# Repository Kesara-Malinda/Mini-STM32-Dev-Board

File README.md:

# Mini-STM32-Dev-Board

Designed using KiCad 6.0

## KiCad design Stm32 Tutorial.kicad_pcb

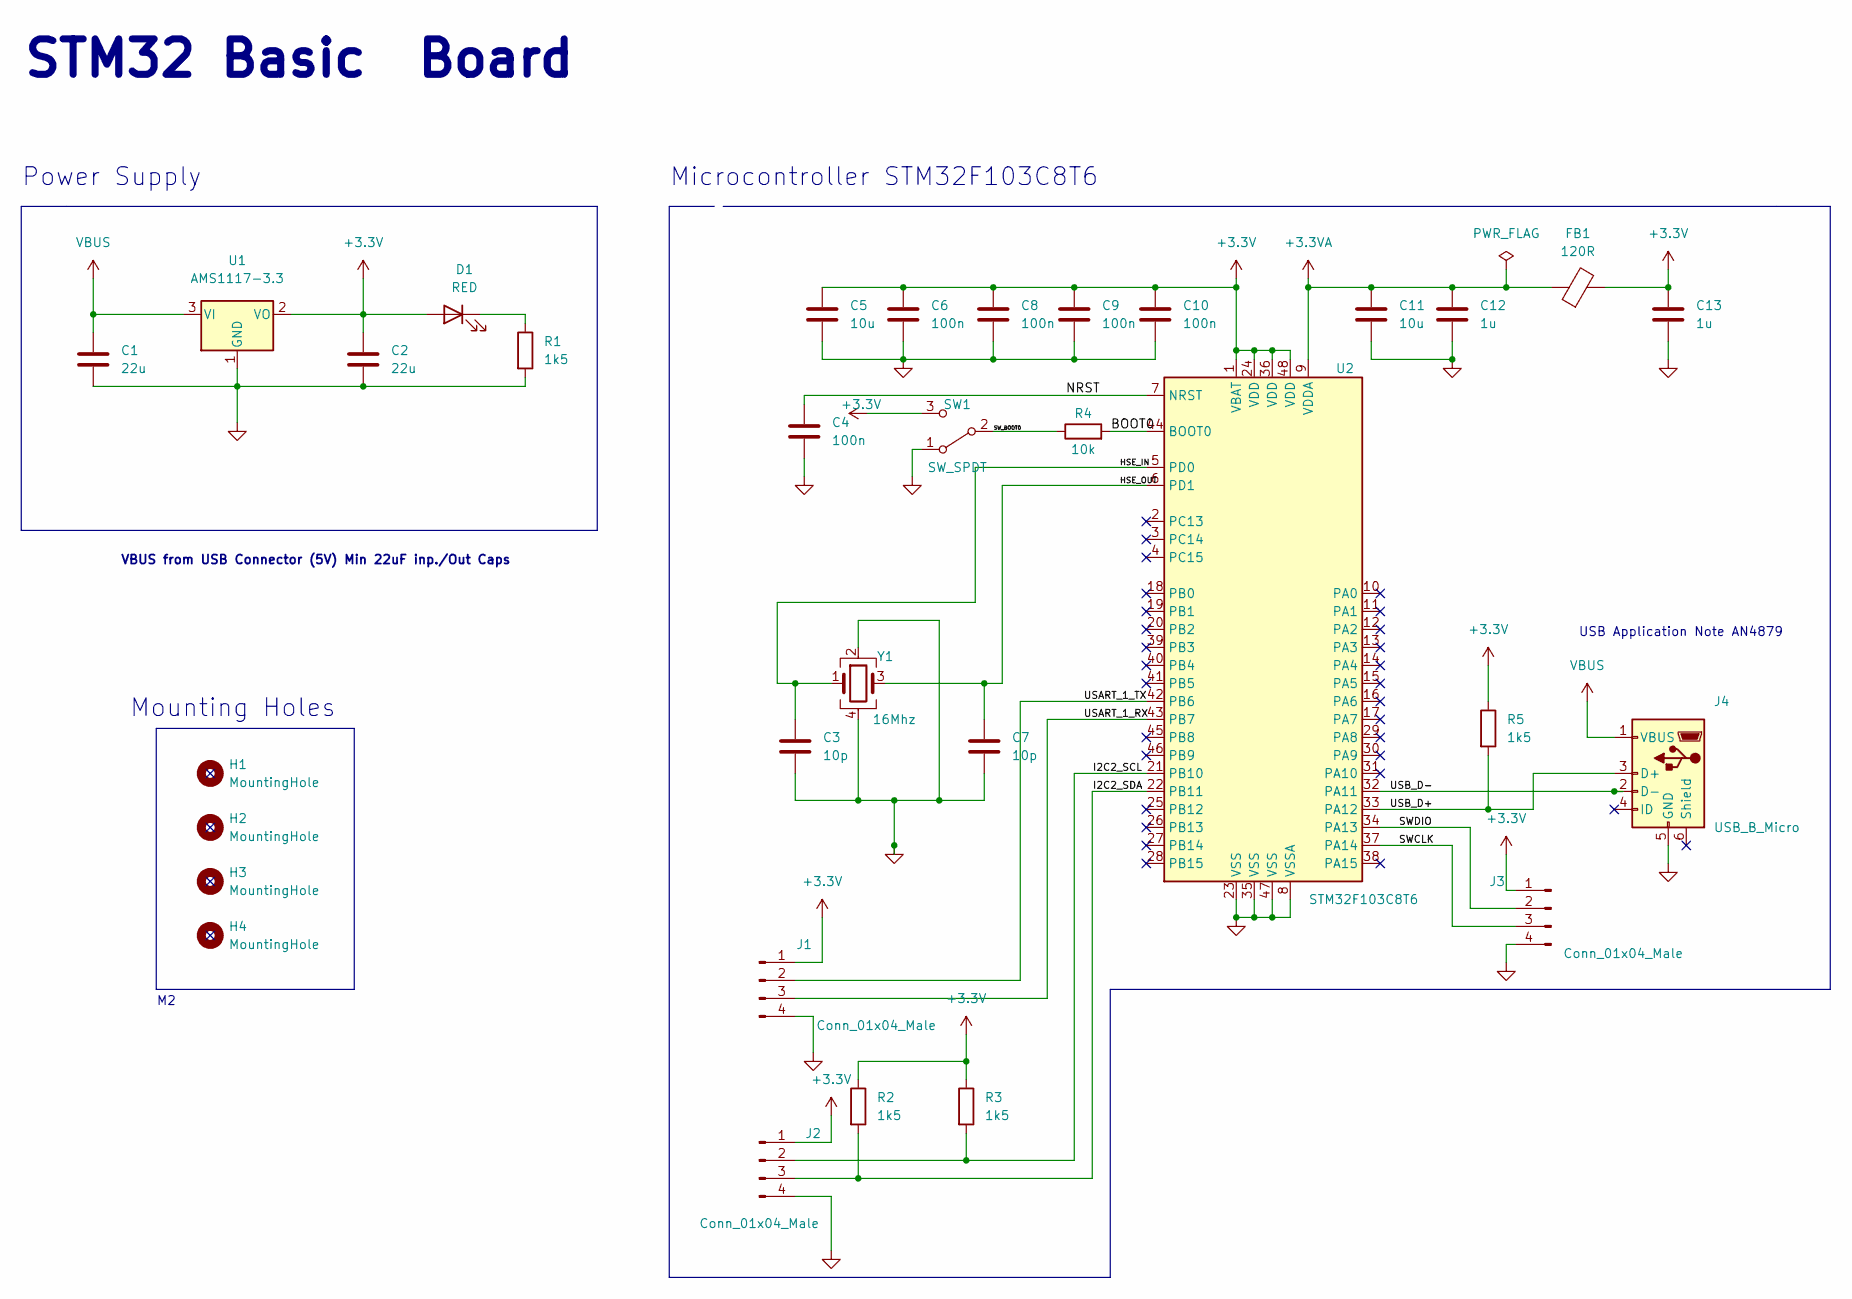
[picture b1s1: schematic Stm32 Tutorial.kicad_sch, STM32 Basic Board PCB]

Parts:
C1, C2: 22u; C_0805_2012Metric
C3, C7: 10p; C_0402_1005Metric
C4, C6, C8, C9, C10: 100n; C_0402_1005Metric
C5: 10u; C_0603_1608Metric
C11: 10u; C_0402_1005Metric
C12, C13: 1u; C_0402_1005Metric
D1: RED; LED_0603_1608Metric
FB1: 120R; L_0603_1608Metric
H1, H2, H3, H4: MountingHole; MountingHole_2.2mm_M2
J1, J2, J3: Conn_01x04_Male; PinHeader_1x04_P2.54mm_Vertical
J4: USB_B_Micro; USB_Micro-B_Wuerth_629105150521
R1, R2, R3, R5: 1k5; R_0402_1005Metric
R4: 10k; R_0402_1005Metric
SW1: SW_SPDT; SW_SPDT_PCM12
U1: AMS1117-3.3; SOT-223-3_TabPin2
U2: STM32F103C8T6; LQFP-48_7x7mm_P0.5mm
Y1: 16Mhz; Crystal_SMD_3225-4Pin_3.2x2.5mm_HandSoldering

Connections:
+3.3V: C2.1, C5.1, C6.1, C8.1, C9.1, C10.1, C13.1, D1.2 (A), FB1.2, J1.1, J2.1, J3.1, R2.1, R3.1, R5.1, SW1.3 (C), U1.2 (VO), U2.1 (VBAT), U2.24 (VDD), U2.36 (VDD), U2.48 (VDD)
+3.3VA: C11.1, C12.1, FB1.1, U2.9 (VDDA)
/BOOT0: R4.2, U2.44 (BOOT0)
/HSE_IN: C3.1, U2.5 (PD0), Y1.1
/HSE_OUT: C7.1, U2.6 (PD1), Y1.3
/I2C2_SCL: J2.2, R3.2, U2.21 (PB10)
/I2C2_SDA: J2.3, R2.2, U2.22 (PB11)
/NRST: C4.1, U2.7 (NRST)
/SWCLK: J3.3, U2.37 (PA14)
/SWDIO: J3.2, U2.34 (PA13)
/SW_BOOT0: R4.1, SW1.2 (B)
/USART_1_RX: J1.3, U2.43 (PB7)
/USART_1_TX: J1.2, U2.42 (PB6)
/USB_D+: J4.3 (D+), R5.2, U2.33 (PA12)
/USB_D-: J4.2 (D-), U2.32 (PA11)
GND: C1.2, C2.2, C3.2, C4.2, C5.2, C6.2, C7.2, C8.2, C9.2, C10.2, C11.2, C12.2, C13.2, J1.4, J2.4, J3.4, J4.5 (GND), J4.6 (Shield), R1.2, SW1.1 (A), U1.1 (GND), U2.8 (VSSA), U2.23 (VSS), U2.35 (VSS), U2.47 (VSS), Y1.2, Y1.4
unnamed: D1.1 (K), R1.1
VBUS: C1.1, J4.1 (VBUS), U1.3 (VI)

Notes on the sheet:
VBUS from USB Connector (5V) Min 22uF inp./Out Caps
Microcontroller STM32F103C8T6
Mounting Holes
USB Application Note AN4879
STM32 Basic Board
Power Supply

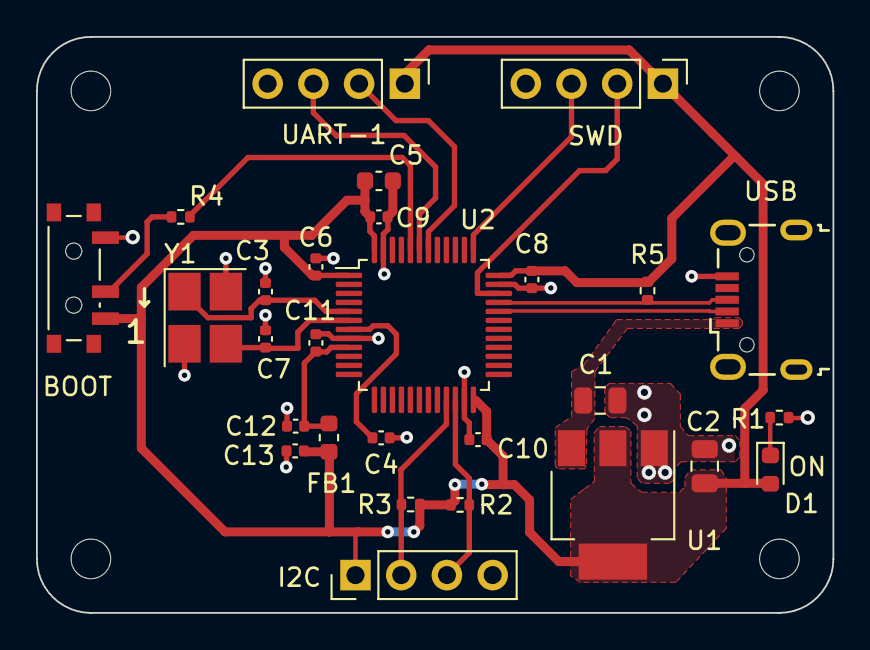
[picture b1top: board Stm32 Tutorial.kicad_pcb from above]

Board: 2 copper layers, 44.2 x 32.0 mm, 32 parts (0 on the bottom side), 18 nets.

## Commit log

2023-12-17 Fixed Missing Track to 3.3V header Pin
2023-12-17 Update README.md
    Updated 3D view and Placement view
